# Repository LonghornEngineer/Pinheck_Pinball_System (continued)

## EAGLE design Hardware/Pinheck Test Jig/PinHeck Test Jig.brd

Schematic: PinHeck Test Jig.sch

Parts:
3.3V, 5V, 12V, 50V: 0914-3-15-20-77-14-11-0
!MCLR!/VPP: POGO_PIN_0914-3-15-20-77-14-11-0; 0914-3-15-20-77-14-11-0
!RES!_PROP: 0914-3-15-20-77-14-11-0
!RST!_PIC32: 0914-3-15-20-77-14-11-0
BACK_OUT: 0914-3-15-20-77-14-11-0
C1, C21, C22, C23, C24: 0.1uF; 0805
C2, C3, C4, C5, C6, C9, C10, C11, C25, C26, C27, C28, C29, C30, C31, C32, C33, C34, C35, C36, C37, C38, C39: 0.1uF; C0603
C7, C8: 47pF; C0603
C12: 4.7uF; CP4MM
C13, C14, C15, C16: 100uF; CP6.3MM
C17, C18, C19, C20: 1uF; C0805
COIN_OUT: 0914-3-15-20-77-14-11-0
DMD_1, DMD_3, DMD_5, DMD_7, DMD_9, DMD_11, DMD_13: 0914-3-15-20-77-14-11-0
DOOR_OUT: 0914-3-15-20-77-14-11-0
ENTER_OUT: 0914-3-15-20-77-14-11-0
EXT_PWR: MF_LED_0805_RED; LED0805
EXT_RGB_CLK: 0914-3-15-20-77-14-11-0
EXT_RGB_DATA: 0914-3-15-20-77-14-11-0
GI_R_0, GI_R_1, GI_R_2, GI_R_3, GI_R_4, GI_R_5, GI_R_6, GI_R_7, GI_R_8, GI_R_9, GI_R_10, GI_R_11, GI_R_12, GI_R_13, GI_R_14, GI_R_15: 0914-3-15-20-77-14-11-0
GND: 0914-3-15-20-77-14-11-0
H1, H2, H3, H4, H5, H6, H7, H8, H9, H10, H11, H12, H13, H14, H15, H16, H17, H18, H19, H20, H21: 2263-2; MOUNT_HOLE_120MIL
ICSPCLK: POGO_PIN_0914-3-15-20-77-14-11-0; 0914-3-15-20-77-14-11-0
ICSPDAT: POGO_PIN_0914-3-15-20-77-14-11-0; 0914-3-15-20-77-14-11-0
J1: USB_MICRO_RIGHT; MICROUSB-RIGHT
J2: DC_PWR_JACK_2.5MM_RIGHT; DC_PWR_JACK
L1: MI0603K300R-10; L0603
LIGHT_C_0, LIGHT_C_1, LIGHT_C_2, LIGHT_C_3, LIGHT_C_4, LIGHT_C_5, LIGHT_C_6, LIGHT_C_7: 0914-3-15-20-77-14-11-0
LIGHT_R_0, LIGHT_R_1, LIGHT_R_2, LIGHT_R_3, LIGHT_R_4, LIGHT_R_5, LIGHT_R_6, LIGHT_R_7: 0914-3-15-20-77-14-11-0
L_FLIP_OUT: 0914-3-15-20-77-14-11-0
OPTO_1_, OPTO_2_, OPTO_3_, OPTO_4_, OPTO_5_, OPTO_6_, OPTO_7_: 0914-3-15-20-77-14-11-0
PGM: POGO_PIN_0914-3-15-20-77-14-11-0; 0914-3-15-20-77-14-11-0
PICKIT3_IN: CON_01X06_2.54MM_PIN_HEADER; 2.54MM_01X06_PIN_HEADER
PROP_AUX0, PROP_AUX1: 0914-3-15-20-77-14-11-0
R1, R2, R3, R4, R5, R9, R22, R23, R24, R25, R26, R27, R28, R29, R31, R32, R33, R34, R35, R36, R37, R38, R39, R40, R41, R42, R43, R44, R45, R46, R47, R48, R49, R50, R51, R52, R53, R54, R55, R56, R57, R58, R59, R60, R61, R62, R63, R64, R65, R66, R67, R68, R69, R70, R71, R72, R73, R74, R75, R76, R77, R78, R79, R80, R81, R82, R83, R84, R93, R94, R97, R98, R99, R100: 10K; R0603
R7, R8: 27; R0603
R10: 470; R0603
R11, R12, R30: 330; R0603
R13: 4.7K; R0603
R14, R15: RL73H2BR10FTD; 1206
R16, R17: ERJ-6ENF3002V; 0805
R18, R19, R20, R21: 10K; 0805
R85, R86, R87, R88, R89, R90, R91, R92: 30K; R0603
RGB_BOUT_L: 0914-3-15-20-77-14-11-0
RGB_BOUT_R: 0914-3-15-20-77-14-11-0
RGB_GOUT_L: 0914-3-15-20-77-14-11-0
RGB_GOUT_R: 0914-3-15-20-77-14-11-0
RGB_ROUT_L: 0914-3-15-20-77-14-11-0
RGB_ROUT_R: 0914-3-15-20-77-14-11-0
RX: MF_LED_0805_RED; LED0805
RX_PIC32: 0914-3-15-20-77-14-11-0
RX_PROP: 0914-3-15-20-77-14-11-0
R_FLIP_OUT: 0914-3-15-20-77-14-11-0
SD_CS: 0914-3-15-20-77-14-11-0
SD_DI: 0914-3-15-20-77-14-11-0
SD_DO: 0914-3-15-20-77-14-11-0
SD_SCLK: 0914-3-15-20-77-14-11-0
SERVO_0_, SERVO_1_, SERVO_2_, SERVO_3_, SERVO_4_: 0914-3-15-20-77-14-11-0
SOL_GND: 0914-3-15-20-77-14-11-0
SOL_PWR_0, SOL_PWR_1, SOL_PWR_2, SOL_PWR_3, SOL_PWR_4, SOL_PWR_5, SOL_PWR_6, SOL_PWR_7, SOL_PWR_8, SOL_PWR_9, SOL_PWR_10, SOL_PWR_11, SOL_PWR_12, SOL_PWR_13, SOL_PWR_14, SOL_PWR_15, SOL_PWR_16, SOL_PWR_17, SOL_PWR_18, SOL_PWR_19, SOL_PWR_20, SOL_PWR_21, SOL_PWR_22, SOL_PWR_23: 0914-3-15-20-77-14-11-0
ST_BU_OUT: 0914-3-15-20-77-14-11-0
ST_LI_: 0914-3-15-20-77-14-11-0
SW_C_0, SW_C_1, SW_C_2, SW_C_3, SW_C_4, SW_C_5, SW_C_6, SW_C_7: 0914-3-15-20-77-14-11-0
SW_R_0, SW_R_1, SW_R_2, SW_R_3, SW_R_4, SW_R_5, SW_R_6, SW_R_7: 0914-3-15-20-77-14-11-0
S_L: 0914-3-15-20-77-14-11-0
S_R: 0914-3-15-20-77-14-11-0
TILT_OUT: 0914-3-15-20-77-14-11-0
TVS1: V18AUMLA2220H; 2220
TX: MF_LED_0805_RED; LED0805
TX_PIC32: 0914-3-15-20-77-14-11-0
TX_PROP: 0914-3-15-20-77-14-11-0
U1: P8X32A-Q44; LQFP44
U2: CAT24C512WI-GT3; SOIC-8_W
U3: FT230XS; SSOP16
U4: IP4234CZ6; IP4234CZ6_SOT-457-6
U5: NCP1117DT33G; NCP1117DT_DPAK-3
U6: NCP1117DT50G; NCP1117DT_DPAK-3
U7, U8: INA139NA/3K; INA169NA/250_SOT-23-5
U9: MAX11613EUA+; MAX11613_UMAX-8
U10, U11: BSO080P03NS3E G; DSO-8
U12, U13: MF-DSC-SOT233-MMBT3904; SOT-23-3
U14, U15: CD74HC595M96; CD74HC595_SOIC-16
U16, U17, U18, U19, U20, U21, U22, U23, U24, U26, U27, U28, U29, U30: CD74HC165M96; CD74HC165_SOIC-16
USB_PWR: MF_LED_0805_RED; LED0805
USER_0_OUT: 0914-3-15-20-77-14-11-0
VDD: POGO_PIN_0914-3-15-20-77-14-11-0; 0914-3-15-20-77-14-11-0
VSS: POGO_PIN_0914-3-15-20-77-14-11-0; 0914-3-15-20-77-14-11-0
X1: ABMM-6.000MHZ-B2-T; 7MMX5MM

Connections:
3.3V: C1.1, C2.P$1, C3.P$1, C4.P$1, C5.P$1, C6.P$1, C11.P$1, C12.P$1, C14.P$1, C18.P$1, C23.1, C24.1, C25.P$1, C26.P$1, C27.P$1, C28.P$1, C29.P$1, C30.P$1, C31.P$1, C32.P$1, C33.P$1, C34.P$1, C35.P$1, C36.P$1, C37.P$1, C38.P$1, C39.P$1, R1.P$1, R2.P$1, R3.P$2, R4.P$2, R5.P$2, R11.P$2, R12.P$2, R22.P$1, R23.P$1, R24.P$1, R25.P$1, R26.P$1, R27.P$1, R28.P$1, R29.P$1, R30.P$2, R31.P$1, R32.P$1, R33.P$1, R34.P$1, R35.P$1, R36.P$1, R37.P$1, R38.P$1, R39.P$1, R40.P$1, R41.P$1, R42.P$1, R43.P$1, R44.P$1, R45.P$1, R46.P$1, R47.P$1, R48.P$1, R49.P$1, R50.P$1, R51.P$1, R52.P$1, R53.P$1, R54.P$1, R55.P$1, R56.P$1, R57.P$1, R58.P$1, R59.P$1, R60.P$1, R61.P$1, R62.P$1, R63.P$1, R64.P$1, R65.P$1, R66.P$1, R67.P$1, R68.P$1, R69.P$1, R70.P$1, R71.P$1, R72.P$1, R73.P$1, R74.P$1, R75.P$1, R76.P$1, R93.P$1, R94.P$1, R97.P$1, R98.P$1, R99.P$1, R100.P$1, U1.8 (VDD), U1.18 (VDD), U1.30 (VDD), U1.40 (VDD), U2.8 (VCC), U3.12 (VCC), U5.TAB (OUT), U7.5 (V+), U8.5 (V+), U9.P$8 (VCC), U14.10 (MR), U14.16 (VCC), U15.10 (MR), U15.16 (VCC), U16.16 (VCC), U17.16 (VCC), U18.16 (VCC), U19.16 (VCC), U20.16 (VCC), U21.16 (VCC), U22.16 (VCC), U23.16 (VCC), U24.16 (VCC), U26.16 (VCC), U27.16 (VCC), U28.16 (VCC), U29.16 (VCC), U30.16 (VCC)
3.3V_SENSE: 3.3V.P$1, U9.P$3 (A_2)
3V3OUT: C10.P$1, U3.3 (VCCIO), U3.10 (3V3OUT), U3.11 (!RESET)
5.0V: C16.P$1, C20.P$1, R15.1, U6.TAB (OUT), U8.3 (VIN+)
5.0V_CUR: R15.2, R20.1, U8.4 (VIN-), U11.5 (DRAIN), U11.6 (DRAIN), U11.7 (DRAIN), U11.8 (DRAIN)
5.0V_SW: 5V.P$1, U11.1 (SOURCE), U11.2 (SOURCE), U11.3 (SOURCE)
12.0V_SW: 12V.P$1, U10.1 (SOURCE), U10.2 (SOURCE), U10.3 (SOURCE)
50V: 50V.P$1
165_CLK: U1.19 (P16), U16.2 (CLK), U17.2 (CLK), U18.2 (CLK), U19.2 (CLK), U20.2 (CLK), U21.2 (CLK), U22.2 (CLK), U23.2 (CLK), U24.2 (CLK), U26.2 (CLK), U27.2 (CLK), U28.2 (CLK), U29.2 (CLK), U30.2 (CLK)
165_DATA: U1.21 (P18), U16.9 (QH)
165_LOAD: U1.20 (P17), U16.1 (LAT), U17.1 (LAT), U18.1 (LAT), U19.1 (LAT), U20.1 (LAT), U21.1 (LAT), U22.1 (LAT), U23.1 (LAT), U24.1 (LAT), U26.1 (LAT), U27.1 (LAT), U28.1 (LAT), U29.1 (LAT), U30.1 (LAT)
595_CLK: U1.22 (P19), U14.11 (SHCP), U15.11 (SHCP)
595_DATA: U1.24 (P21), U14.14 (DS)
595_LAT: U1.23 (P20), U14.12 (STCP), U15.12 (STCP)
!RES!_PROP: !RES!_PROP.P$1, U1.12 (P11)
!RST!_PIC32: !RST!_PIC32.P$1, U1.9 (P8)
A_0: C21.1, R16.2, U7.1 (OUT), U9.P$1 (A_0)
A_1: C22.1, R17.2, U8.1 (OUT), U9.P$2 (A_1)
BACK_OUT: BACK_OUT.P$1, U14.4 (Q4)
COIN_OUT: COIN_OUT.P$1, U14.2 (Q2)
D+_USB: J1.3 (D+), U4.1 (I/O1A)
D-_USB: J1.2 (D-), U4.6 (I/O2A)
DMD_1: DMD_1.P$1, U29.13 (D2)
DMD_3: DMD_3.P$1, U29.14 (D3)
DMD_5: DMD_5.P$1, U29.3 (D4)
DMD_7: DMD_7.P$1, U29.4 (D5)
DMD_9: DMD_9.P$1, U29.5 (D6)
DMD_11: DMD_11.P$1, U29.6 (D7)
DMD_13: DMD_13.P$1, U30.11 (D0)
DOOR_OUT: DOOR_OUT.P$1, U14.5 (Q5)
ENTER_OUT: ENTER_OUT.P$1, U14.3 (Q3)
EXT_RGB_CLK: EXT_RGB_CLK.P$1, U28.11 (D0)
EXT_RGB_DATA: EXT_RGB_DATA.P$1, U28.12 (D1)
GI15: GI_R_15.P$1, R28.P$2, U18.11 (D0)
GI_R_0: GI_R_0.P$1, R27.P$2, U17.6 (D7)
GI_R_1: GI_R_1.P$1, R26.P$2, U17.5 (D6)
GI_R_2: GI_R_2.P$1, R25.P$2, U17.4 (D5)
GI_R_3: GI_R_3.P$1, R24.P$2, U17.3 (D4)
GI_R_4: GI_R_4.P$1, R23.P$2, U17.14 (D3)
GI_R_5: GI_R_5.P$1, R22.P$2, U17.13 (D2)
GI_R_6: GI_R_6.P$1, R2.P$2, U17.12 (D1)
GI_R_7: GI_R_7.P$1, R1.P$2, U17.11 (D0)
GI_R_8: GI_R_8.P$1, R36.P$2, U18.6 (D7)
GI_R_9: GI_R_9.P$1, R35.P$2, U18.5 (D6)
GI_R_10: GI_R_10.P$1, R34.P$2, U18.4 (D5)
GI_R_11: GI_R_11.P$1, R33.P$2, U18.3 (D4)
GI_R_12: GI_R_12.P$1, R32.P$2, U18.14 (D3)
GI_R_13: GI_R_13.P$1, R31.P$2, U18.13 (D2)
GI_R_14: GI_R_14.P$1, R29.P$2, U18.12 (D1)
GND: C1.2, C2.P$2, C3.P$2, C4.P$2, C5.P$2, C6.P$2, C7.P$2, C8.P$2, C10.P$2, C11.P$2, C12.P$2, C13.P$2, C14.P$2, C15.P$2, C16.P$2, C17.P$2, C18.P$2, C19.P$2, C20.P$2, C21.2, C22.2, C23.2, C24.2, C25.P$2, C26.P$2, C27.P$2, C28.P$2, C29.P$2, C30.P$2, C31.P$2, C32.P$2, C33.P$2, C34.P$2, C35.P$2, C36.P$2, C37.P$2, C38.P$2, C39.P$2, EXT_PWR.CATHODE, GND.P$1, J1.5 (GND), J2.SLEEVE1 (SLEEVE), J2.SLEEVE2 (SLEEVE_SHUNT), L1.P$2, R9.P$1, R16.1, R17.1, R77.P$1, R78.P$1, R79.P$1, R80.P$1, R81.P$1, R82.P$1, R83.P$1, R84.P$1, SOL_GND.P$1, TVS1.P$2, U1.5 (VSS), U1.6 (BOE'), U1.17 (VSS), U1.27 (VSS), U1.39 (VSS), U2.2 (A1), U2.3 (A2), U2.4 (GND), U2.7 (WP), U3.5 (GND), U3.13 (GND), U4.2 (GND), U5.1 (GND), U6.1 (GND), U7.2 (GND), U8.2 (GND), U9.P$7 (GND), U12.2 (EMITTER), U13.2 (EMITTER), U14.8 (GND), U14.13 (OE), U15.8 (GND), U15.13 (OE), U16.8 (GND), U16.15 (C_INH), U17.8 (GND), U17.15 (C_INH), U18.8 (GND), U18.15 (C_INH), U19.8 (GND), U19.15 (C_INH), U20.8 (GND), U20.15 (C_INH), U21.8 (GND), U21.15 (C_INH), U22.8 (GND), U22.15 (C_INH), U23.8 (GND), U23.15 (C_INH), U24.8 (GND), U24.15 (C_INH), U26.8 (GND), U26.15 (C_INH), U27.8 (GND), U27.15 (C_INH), U28.8 (GND), U28.15 (C_INH), U29.8 (GND), U29.15 (C_INH), U30.8 (GND), U30.15 (C_INH), USB_PWR.CATHODE, X1.P$2 (GND), X1.P$4 (GND)
LIGHT_C_0: LIGHT_C_0.P$1, R85.P$2
LIGHT_C_1: LIGHT_C_1.P$1, R86.P$2
LIGHT_C_2: LIGHT_C_2.P$1, R87.P$2
LIGHT_C_3: LIGHT_C_3.P$1, R88.P$2
LIGHT_C_4: LIGHT_C_4.P$1, R89.P$2
LIGHT_C_5: LIGHT_C_5.P$1, R90.P$2
LIGHT_C_6: LIGHT_C_6.P$1, R91.P$2
LIGHT_C_7: LIGHT_C_7.P$1, R92.P$2
LIGHT_R_0: LIGHT_R_0.P$1, R76.P$2, U23.6 (D7)
LIGHT_R_1: LIGHT_R_1.P$1, R75.P$2, U23.5 (D6)
LIGHT_R_2: LIGHT_R_2.P$1, R74.P$2, U23.4 (D5)
LIGHT_R_3: LIGHT_R_3.P$1, R73.P$2, U23.3 (D4)
LIGHT_R_4: LIGHT_R_4.P$1, R72.P$2, U23.14 (D3)
LIGHT_R_5: LIGHT_R_5.P$1, R71.P$2, U23.13 (D2)
LIGHT_R_6: LIGHT_R_6.P$1, R70.P$2, U23.12 (D1)
LIGHT_R_7: LIGHT_R_7.P$1, R69.P$2, U23.11 (D0)
L_FLIP_OUT: L_FLIP_OUT.P$1, U14.15 (Q0)
unnamed: U18.10 (SER), U19.9 (QH)
unnamed: U19.10 (SER), U20.9 (QH)
unnamed: R7.P$2, U3.9 (USBDM)
unnamed: R8.P$2, U3.8 (USBDP)
unnamed: C7.P$1, R7.P$1, U4.4 (I/O2B)
unnamed: C8.P$1, R8.P$1, U4.3 (I/O1B)
unnamed: R10.P$1, USB_PWR.ANODE
unnamed: R11.P$1, TX.ANODE
unnamed: R12.P$1, RX.ANODE
unnamed: R18.2, U10.4 (GATE), U12.3 (COLLECTOR)
unnamed: R20.2, U11.4 (GATE), U13.3 (COLLECTOR)
unnamed: R19.2, U12.1 (BASE)
unnamed: U20.10 (SER), U21.9 (QH)
unnamed: R21.2, U13.1 (BASE)
unnamed: U21.10 (SER), U22.9 (QH)
unnamed: U22.10 (SER), U23.9 (QH)
unnamed: U23.10 (SER), U24.9 (QH)
unnamed: U14.9 (Q7S), U15.14 (DS)
unnamed: U16.10 (SER), U17.9 (QH)
unnamed: U24.10 (SER), U26.9 (QH)
unnamed: U17.10 (SER), U18.9 (QH)
unnamed: U26.10 (SER), U27.9 (QH)
unnamed: U27.10 (SER), U28.9 (QH)
unnamed: U28.10 (SER), U29.9 (QH)
unnamed: U29.10 (SER), U30.9 (QH)
unnamed: R84.P$2, R92.P$1, U24.11 (D0)
unnamed: !MCLR!/VPP.P$1, PICKIT3_IN.1
unnamed: PICKIT3_IN.2, VDD.P$1
unnamed: EXT_PWR.ANODE, R30.P$1
unnamed: PICKIT3_IN.3, VSS.P$1
unnamed: ICSPDAT.P$1, PICKIT3_IN.4
unnamed: ICSPCLK.P$1, PICKIT3_IN.5
unnamed: PGM.P$1, PICKIT3_IN.6
unnamed: R83.P$2, R91.P$1, U24.12 (D1)
unnamed: R82.P$2, R90.P$1, U24.13 (D2)
unnamed: R81.P$2, R89.P$1, U24.14 (D3)
unnamed: R80.P$2, R88.P$1, U24.3 (D4)
unnamed: R79.P$2, R87.P$1, U24.4 (D5)
unnamed: R78.P$2, R86.P$1, U24.5 (D6)
unnamed: R77.P$2, R85.P$1, U24.6 (D7)
OPTO_1: OPTO_1_.P$1, U26.11 (D0)
OPTO_2: OPTO_2_.P$1, U26.12 (D1)
OPTO_3: OPTO_3_.P$1, U26.13 (D2)
OPTO_4: OPTO_4_.P$1, U26.14 (D3)
OPTO_5: OPTO_5_.P$1, U26.3 (D4)
OPTO_6: OPTO_6_.P$1, U26.4 (D5)
OPTO_7: OPTO_7_.P$1, U26.5 (D6)
P1: U1.42 (P1)
P2: U1.43 (P2)
P3: U1.44 (P3)
P4: U1.1 (P4)
P5: U1.2 (P5)
P6: U1.3 (P6)
P7: U1.4 (P7)
P14: U1.15 (P14)
P15: U1.16 (P15)
P22: U1.25 (P22)
P23: U1.26 (P23)
P24: U1.31 (P24)
P25: U1.32 (P25)
P26: U1.33 (P26)
P27: U1.34 (P27)
PROP_!RST: C9.P$2, R5.P$1, U1.7 (RES')
PROP_AUX0: PROP_AUX0.P$1, U28.13 (D2)
PROP_AUX1: PROP_AUX1.P$1, U28.14 (D3)
PWR_ON: R19.1, R21.1, U1.41 (P0)
RGB_BOUT_L: R94.P$2, RGB_BOUT_L.P$1, U29.12 (D1)
RGB_BOUT_R: R99.P$2, RGB_BOUT_R.P$1, U28.5 (D6)
RGB_GOUT_L: R93.P$2, RGB_GOUT_L.P$1, U29.11 (D0)
RGB_GOUT_R: R98.P$2, RGB_GOUT_R.P$1, U28.4 (D5)
RGB_ROUT_L: R100.P$2, RGB_ROUT_L.P$1, U28.6 (D7)
RGB_ROUT_R: R97.P$2, RGB_ROUT_R.P$1, U28.3 (D4)
RX: U1.37 (P30), U3.4 (RXD)
RX_LED: RX.CATHODE, U3.14 (CBUS1)
RX_PIC32: RX_PIC32.P$1, U1.11 (P10)
RX_PROP: RX_PROP.P$1, U1.14 (P13)
R_FLIP_OUT: R_FLIP_OUT.P$1, U14.7 (Q7)
SCL: R3.P$1, U1.35 (P28), U2.6 (SCL), U9.P$5 (SCL)
SDA: R4.P$1, U1.36 (P29), U2.5 (SDA), U9.P$6 (SDA)
SD_CS: SD_CS.P$1, U16.11 (D0)
SD_DI: SD_DI.P$1, U16.12 (D1)
SD_DO: SD_DO.P$1, U16.14 (D3)
SD_SCLK: SD_SCLK.P$1, U16.13 (D2)
SERVO_0: SERVO_0_.P$1, U27.11 (D0)
SERVO_1: SERVO_1_.P$1, U27.12 (D1)
SERVO_2: SERVO_2_.P$1, U27.13 (D2)
SERVO_3: SERVO_3_.P$1, U27.14 (D3)
SERVO_4: SERVO_4_.P$1, U27.3 (D4)
SHIELD: J1.S3 (SLD), J1.S4 (SLD), J1.S5 (SLD), J1.S6 (SLD), L1.P$1
SOL_PWR_0: R60.P$2, SOL_PWR_0.P$1, U21.6 (D7)
SOL_PWR_1: R59.P$2, SOL_PWR_1.P$1, U21.5 (D6)
SOL_PWR_2: R58.P$2, SOL_PWR_2.P$1, U21.4 (D5)
SOL_PWR_3: R57.P$2, SOL_PWR_3.P$1, U21.3 (D4)
SOL_PWR_4: R56.P$2, SOL_PWR_4.P$1, U21.14 (D3)
SOL_PWR_5: R55.P$2, SOL_PWR_5.P$1, U21.13 (D2)
SOL_PWR_6: R54.P$2, SOL_PWR_6.P$1, U21.12 (D1)
SOL_PWR_7: R53.P$2, SOL_PWR_7.P$1, U21.11 (D0)
SOL_PWR_8: R52.P$2, SOL_PWR_8.P$1, U20.6 (D7)
SOL_PWR_9: R51.P$2, SOL_PWR_9.P$1, U20.5 (D6)
SOL_PWR_10: R50.P$2, SOL_PWR_10.P$1, U20.4 (D5)
SOL_PWR_11: R49.P$2, SOL_PWR_11.P$1, U20.3 (D4)
SOL_PWR_12: R48.P$2, SOL_PWR_12.P$1, U20.14 (D3)
SOL_PWR_13: R47.P$2, SOL_PWR_13.P$1, U20.13 (D2)
SOL_PWR_14: R46.P$2, SOL_PWR_14.P$1, U20.12 (D1)
SOL_PWR_15: R45.P$2, SOL_PWR_15.P$1, U20.11 (D0)
SOL_PWR_16: R44.P$2, SOL_PWR_16.P$1, U19.6 (D7)
SOL_PWR_17: R43.P$2, SOL_PWR_17.P$1, U19.5 (D6)
SOL_PWR_18: R42.P$2, SOL_PWR_18.P$1, U19.4 (D5)
SOL_PWR_19: R41.P$2, SOL_PWR_19.P$1, U19.3 (D4)
SOL_PWR_20: R40.P$2, SOL_PWR_20.P$1, U19.14 (D3)
SOL_PWR_21: R39.P$2, SOL_PWR_21.P$1, U19.13 (D2)
SOL_PWR_22: R38.P$2, SOL_PWR_22.P$1, U19.12 (D1)
SOL_PWR_23: R37.P$2, SOL_PWR_23.P$1, U19.11 (D0)
ST_BU_OUT: ST_BU_OUT.P$1
ST_LI: ST_LI_.P$1, U16.5 (D6)
SW_C_0: R61.P$2, SW_C_0.P$1, U22.11 (D0)
SW_C_1: R62.P$2, SW_C_1.P$1, U22.12 (D1)
SW_C_2: R63.P$2, SW_C_2.P$1, U22.13 (D2)
SW_C_3: R64.P$2, SW_C_3.P$1, U22.14 (D3)
SW_C_4: R65.P$2, SW_C_4.P$1, U22.3 (D4)
SW_C_5: R66.P$2, SW_C_5.P$1, U22.4 (D5)
SW_C_6: R67.P$2, SW_C_6.P$1, U22.5 (D6)
SW_C_7: R68.P$2, SW_C_7.P$1, U22.6 (D7)
SW_R_0: SW_R_0.P$1, U15.7 (Q7)
SW_R_1: SW_R_1.P$1, U15.6 (Q6)
SW_R_2: SW_R_2.P$1, U15.5 (Q5)
SW_R_3: SW_R_3.P$1, U15.4 (Q4)
SW_R_4: SW_R_4.P$1, U15.3 (Q3)
SW_R_5: SW_R_5.P$1, U15.2 (Q2)
SW_R_6: SW_R_6.P$1, U15.1 (Q1)
SW_R_7: SW_R_7.P$1, U15.15 (Q0)
S_L: S_L.P$1, U16.3 (D4)
S_R: S_R.P$1, U16.4 (D5)
TILT_OUT: TILT_OUT.P$1, U14.1 (Q1)
TX: U1.38 (P31), U3.1 (TXD)
TX_LED: TX.CATHODE, U3.15 (CBUS0)
TX_PIC32: TX_PIC32.P$1, U1.10 (P9)
TX_PROP: TX_PROP.P$1, U1.13 (P12)
USB_!RST: C9.P$1, U3.2 (!RTS)
USER_0_OUT: U14.6 (Q6), USER_0_OUT.P$1
VBUS_SENSE: R9.P$2, R13.P$1, U3.16 (CBUS3)
VIN: C13.P$1, C15.P$1, C17.P$1, C19.P$1, J2.PIN, R14.1, TVS1.P$1, U5.3 (IN), U6.3 (IN), U7.3 (VIN+)
VIN_CUR: R14.2, R18.1, U7.4 (VIN-), U10.5 (DRAIN), U10.6 (DRAIN), U10.7 (DRAIN), U10.8 (DRAIN)
V_USB_0: J1.1 (5V), R10.P$2, R13.P$2, U4.5 (VB)
X0: U1.29 (X0), X1.P$1 (X0)
X1: U1.28 (X1), X1.P$3 (X1)

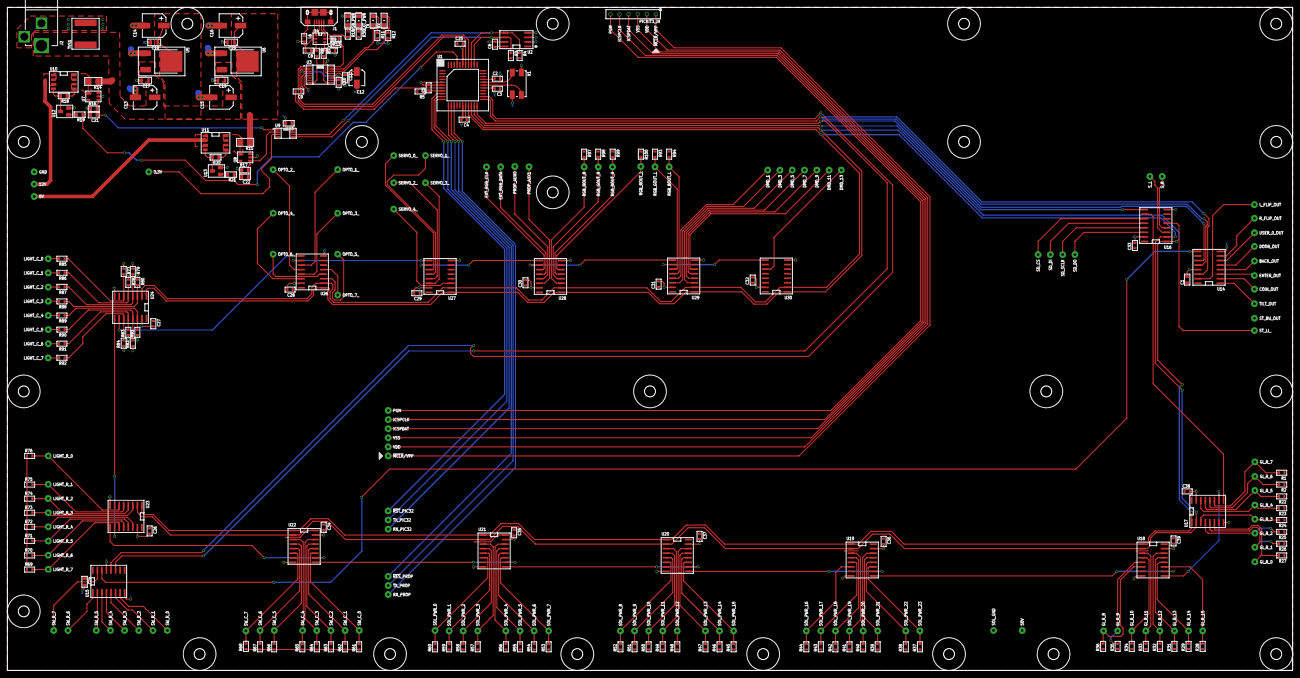
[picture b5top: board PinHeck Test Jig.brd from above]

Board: 2 copper layers, 359.2 x 185.3 mm, 331 parts (0 on the bottom side), 196 nets.

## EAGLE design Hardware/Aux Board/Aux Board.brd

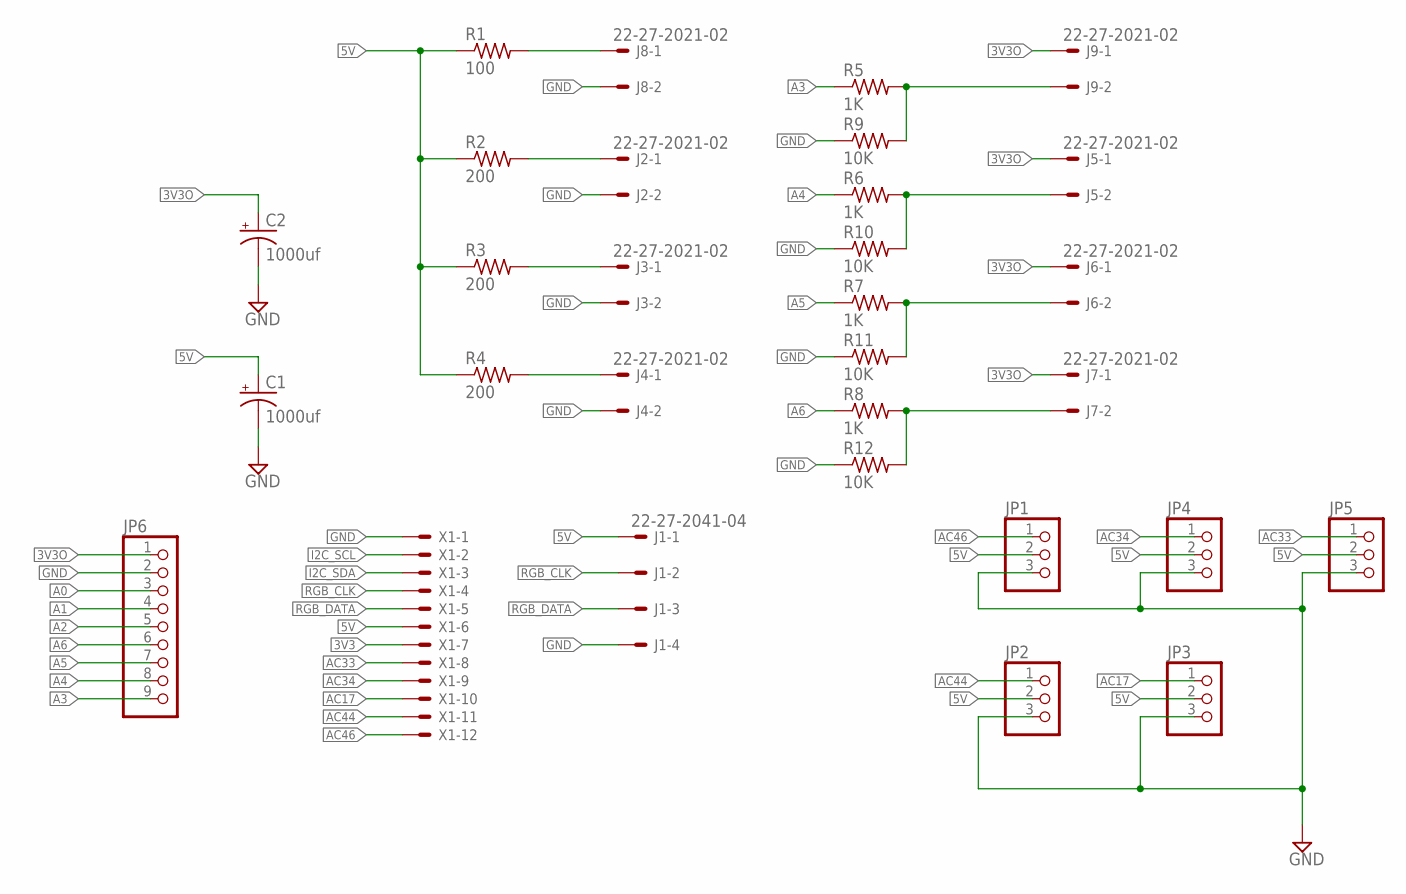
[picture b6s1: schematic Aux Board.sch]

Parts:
C1, C2: 1000uf; E5-8,5
J1: 22-27-2041-04; 6410-04
J2, J3, J4, J5, J6, J7, J8, J9: 22-27-2021-02; 6410-02
JP1, JP2, JP3, JP4, JP5: PINHD-1X3; 1X03
JP6: PINHD-1X9; 1X09-BIG
R1: 100; 0207/10
R2, R3, R4: 200; 0207/10
R5, R6, R7, R8: 1K; 0207/10
R9, R10, R11, R12: 10K; 0207/10
X1: KK-156-12

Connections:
3V3: X1.7
3V3O: C2.+, J5.1, J6.1, J7.1, J9.1, JP6.1
5V: C1.+, J1.1, JP1.2, JP2.2, JP3.2, JP4.2, JP5.2, R1.1, R2.1, R3.1, R4.1, X1.6
A0: JP6.3
A1: JP6.4
A2: JP6.5
A3: JP6.9, R5.1
A4: JP6.8, R6.1
A5: JP6.7, R7.1
A6: JP6.6, R8.1
AC17: JP3.1, X1.10
AC33: JP5.1, X1.8
AC34: JP4.1, X1.9
AC44: JP2.1, X1.11
AC46: JP1.1, X1.12
GND: C1.-, C2.-, J1.4, J2.2, J3.2, J4.2, J8.2, JP1.3, JP2.3, JP3.3, JP4.3, JP5.3, JP6.2, R9.1, R10.1, R11.1, R12.1, X1.1
I2C_SCL: X1.2
I2C_SDA: X1.3
unnamed: J7.2, R8.2, R12.2
unnamed: J6.2, R7.2, R11.2
unnamed: J5.2, R6.2, R10.2
unnamed: J2.1, R2.2
unnamed: J3.1, R3.2
unnamed: J4.1, R4.2
unnamed: J9.2, R5.2, R9.2
unnamed: J8.1, R1.2
RGB_CLK: J1.2, X1.4
RGB_DATA: J1.3, X1.5

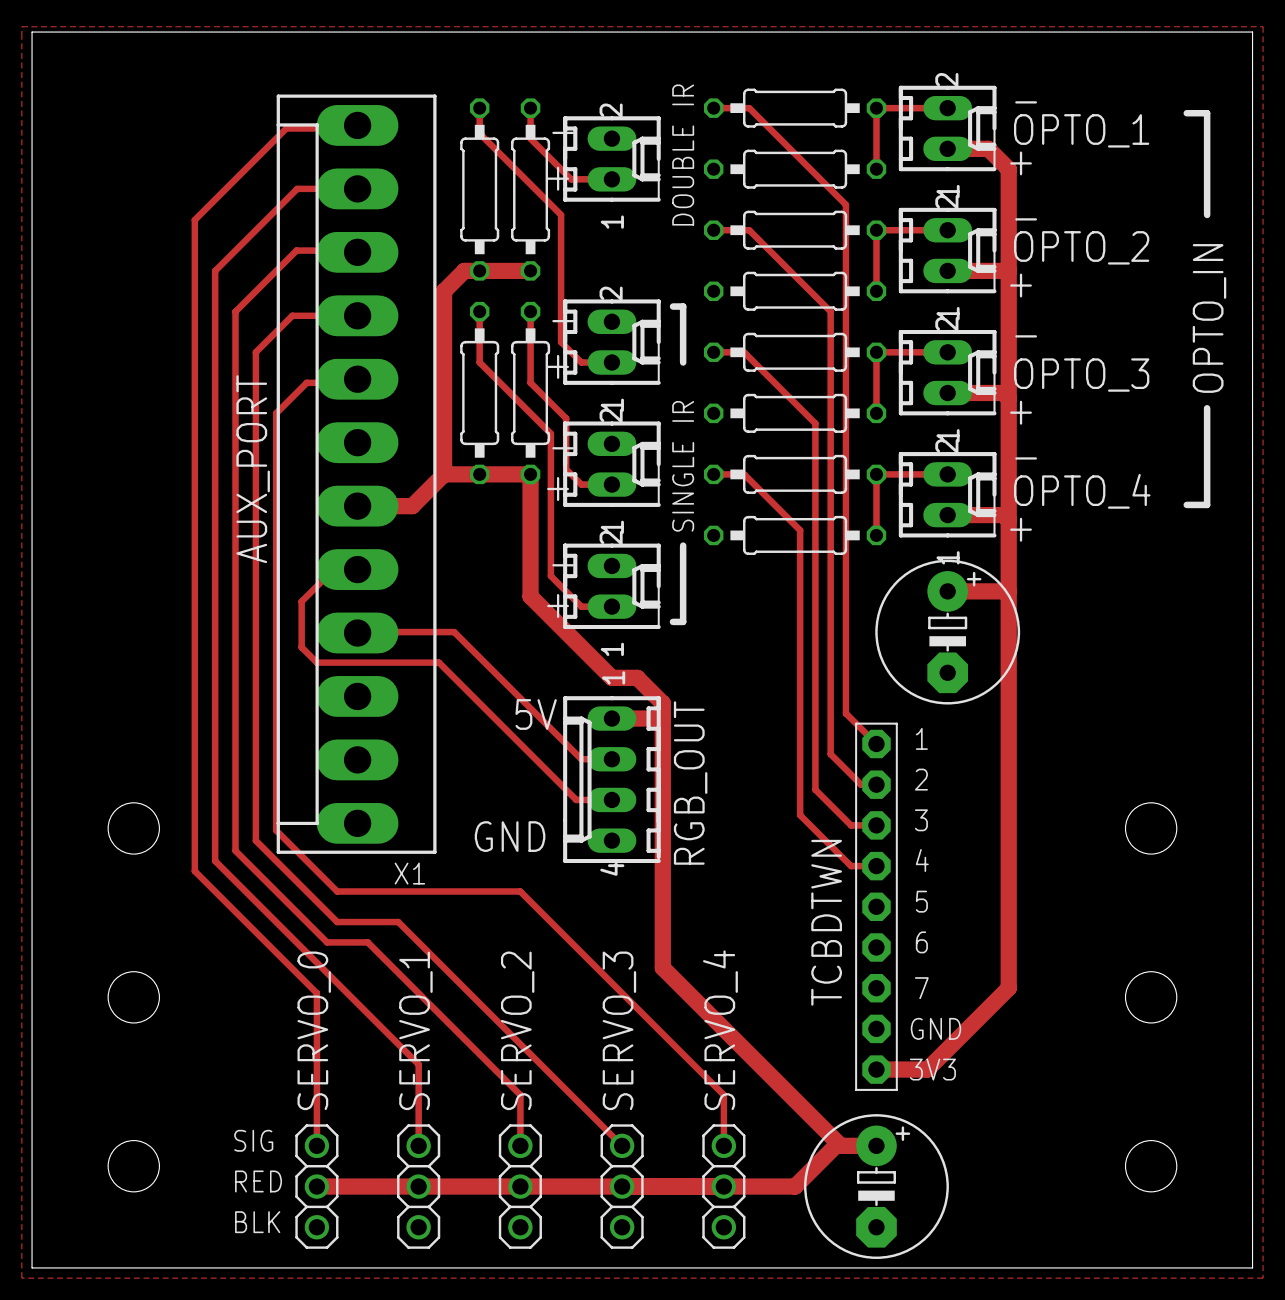
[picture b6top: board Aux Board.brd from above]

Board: 4 copper layers, 76.2 x 77.1 mm, 30 parts (0 on the bottom side), 22 nets.

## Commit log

2013-10-22 First revision push.
2013-10-22 deleting files
2013-10-22 Added chipkit design files for reference.
2013-10-25 Changed the alphanumeric display to be GI.
2013-10-26 Changed Watchdog timer to work via 555timer
2013-10-26 Fixing some layout issues. Added some breakouts.
2013-10-26 changed port name. added new layout pic.
2013-10-29 New Spooky Logo
2013-11-13 Fixed spacing errors.
2013-12-06 Fixed Bill of Material Issues
2013-12-06 Fixed Part Names
2013-12-11 Rev 5 push. Fixed Bom issues and pinout for 556.
2013-12-17 Changed some resistors to there correct number.
2013-12-30 Changed LEDs to 0805 package.
2014-01-03 Bootloader for the PIC32
2014-01-08 Updated Bill of Materials.
2014-01-14 Swapped LAT and CLK on 595. FIXED.
2014-01-19 Changed names for unused IO
2014-01-23 Added Bluetooth
2014-01-23 Added 2 more audio channels
2014-01-23 Added MF Logo
2014-01-27 Swapped TX/RX on BT module.
2014-01-27 Updated board layout a bit.
2014-02-10 Fixed TO-220 Hole diameter size.
2014-02-10 Finished Layout image
2014-02-24 Updated BOM
2014-02-24 Tweaked BOM script to clean up.
2014-03-24 Added FT230X Template
2014-04-09 Update to CC-BY-SA License.
2014-12-23 Neo Pixel Support and Increased 5V OF DOOM
2015-02-07 Beefed up 5V line, added caps, added AUX power con.
2015-02-07 Changed REV number to 6
2015-02-26 Adding PNG of Schematic
2015-04-27 Adjusting file structure and adding Opto
2015-12-09 REV7 START
2015-12-10 EEPROM fixed, New mounting hole sizes.
2015-12-10 Changing out connectors.
2015-12-10 Updating more connectors!
2015-12-14 Updated Parts to new library style!
2015-12-15 Working on Layout now.
2015-12-20 Part changes and new features added. Time to route.
2015-12-20 Starting layout of parts and connectors
2015-12-21 Layout of parts almost done. Needs some tweaking but everything fits.
2015-12-21 Upped DRC to 6 layer and added inner power planes.
2015-12-21 Routing the solenoid power area.
2015-12-21 Added opto files.
2015-12-21 Fixed polygon.
2015-12-22 Added changes for Ben
2015-12-27 Routing external connectors first. Working my way inwards.
2015-12-28 have all the peripherals layed out on the new pinheck
2015-12-28 Prop routed. Pic32 started.
2015-12-28 Home stretch!
2015-12-29 MOD CON area done. Starting test header.
2015-12-29 First draft layout complete. Still need to wire in edge connector.
2015-12-29 Added Shaker connector.
2015-12-29 Added RGB_COM_OUT_1
2015-12-29 Added more things to PHAM.
2016-01-02 Adding fuses.
2016-01-04 TPS chips added and fuses added.
2016-01-05 started edge con routing.
2016-01-11 more routing!
2016-01-15 Layout done. Silkscreen and TP to do!
2016-01-15 Started Test Points
2016-01-15 Test points almost done!
2016-01-16 finished test points.
2016-01-16 Layout complete and silkscreen almost done!
2016-01-17 Silkscreen done.
2016-01-18 REV 7 preliminary done.
2016-01-22 Added AUX power Connector
2016-01-24 pushing first of test jig.
2016-01-26 Added AUX, and RGB LED Board. Working on Test Jib.
2016-01-26 Jig Schematic Done.
2016-01-26 Routing Test Jig.
2016-01-27 Still routing!
2016-01-27 More work done. Fixed size issue.
2016-01-29 Almost done!
2016-01-29 routing almost done.
2016-01-29 Almost done.
    Need to change drill size.
2016-01-30 Test Jig done.
2016-02-03 Added mounting plate for Pinheck
2016-02-07 Added 1M pullup to EN pin on the TPS25925x/6x
2016-02-07 Fixed 4628
2016-02-11 Fixed Pinheaders
2016-02-11 Added LED Fuse Indicators and BATT POS mark
2016-02-16 Adding new licensing information for the hardware.
2016-02-25 Working on Test Jig Code.
2016-02-29 Added silkscreen.
2016-03-31 changed LED to CLY6D-FKC-CK1N1D1BB7D3D3
2016-04-12 Test Jig software. WIP
2016-04-12 GI and Solenoids working. WIP
2016-04-13 Preliminary Code Done. Need PROP testing.
2016-04-13 Fixed issue with non init pins.
2016-04-18 Test code for the PROP complete. Needs testing on the Fixture.
2016-04-19 Added code to make Prop Program Prop!
2016-04-19 Test code now programs and tests Prop side.
2016-04-21 Added EXT RGB testing and OPTO testing.
2016-04-27 Working on changes for REV 7C
    Changed Audio connector to SJ1-3533NS
2016-04-27 Fixed Start LED
2016-08-24 Starting S^3
2016-12-13 tone control done.
2016-12-13 PinHeck REV7D. Changed Battery connector.
2016-12-13 Schematic done. Start Routing.
2017-01-25 Starting layout...
2017-01-26 Parts layed out
2017-01-31 routing about halfway finished.
2017-02-01 Initial routing done.
2017-02-02 Cleaning up the routing...
2017-02-02 New Layout Image.
2017-02-08 Finished routing
    Just needs tweaking and final look over.
2017-03-28 adding RPI3 LVDS board.
2017-03-28 Uploading camfiles and manufacturing data.
2017-04-21 Fixed LM1085
2017-04-21 updated manufacturing files.
2019-01-15 Removing older boards
